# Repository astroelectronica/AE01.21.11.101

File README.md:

# AE01.21.11.101
MCP4531T-103E/MS
Basic configuration for Arduino UNO R3

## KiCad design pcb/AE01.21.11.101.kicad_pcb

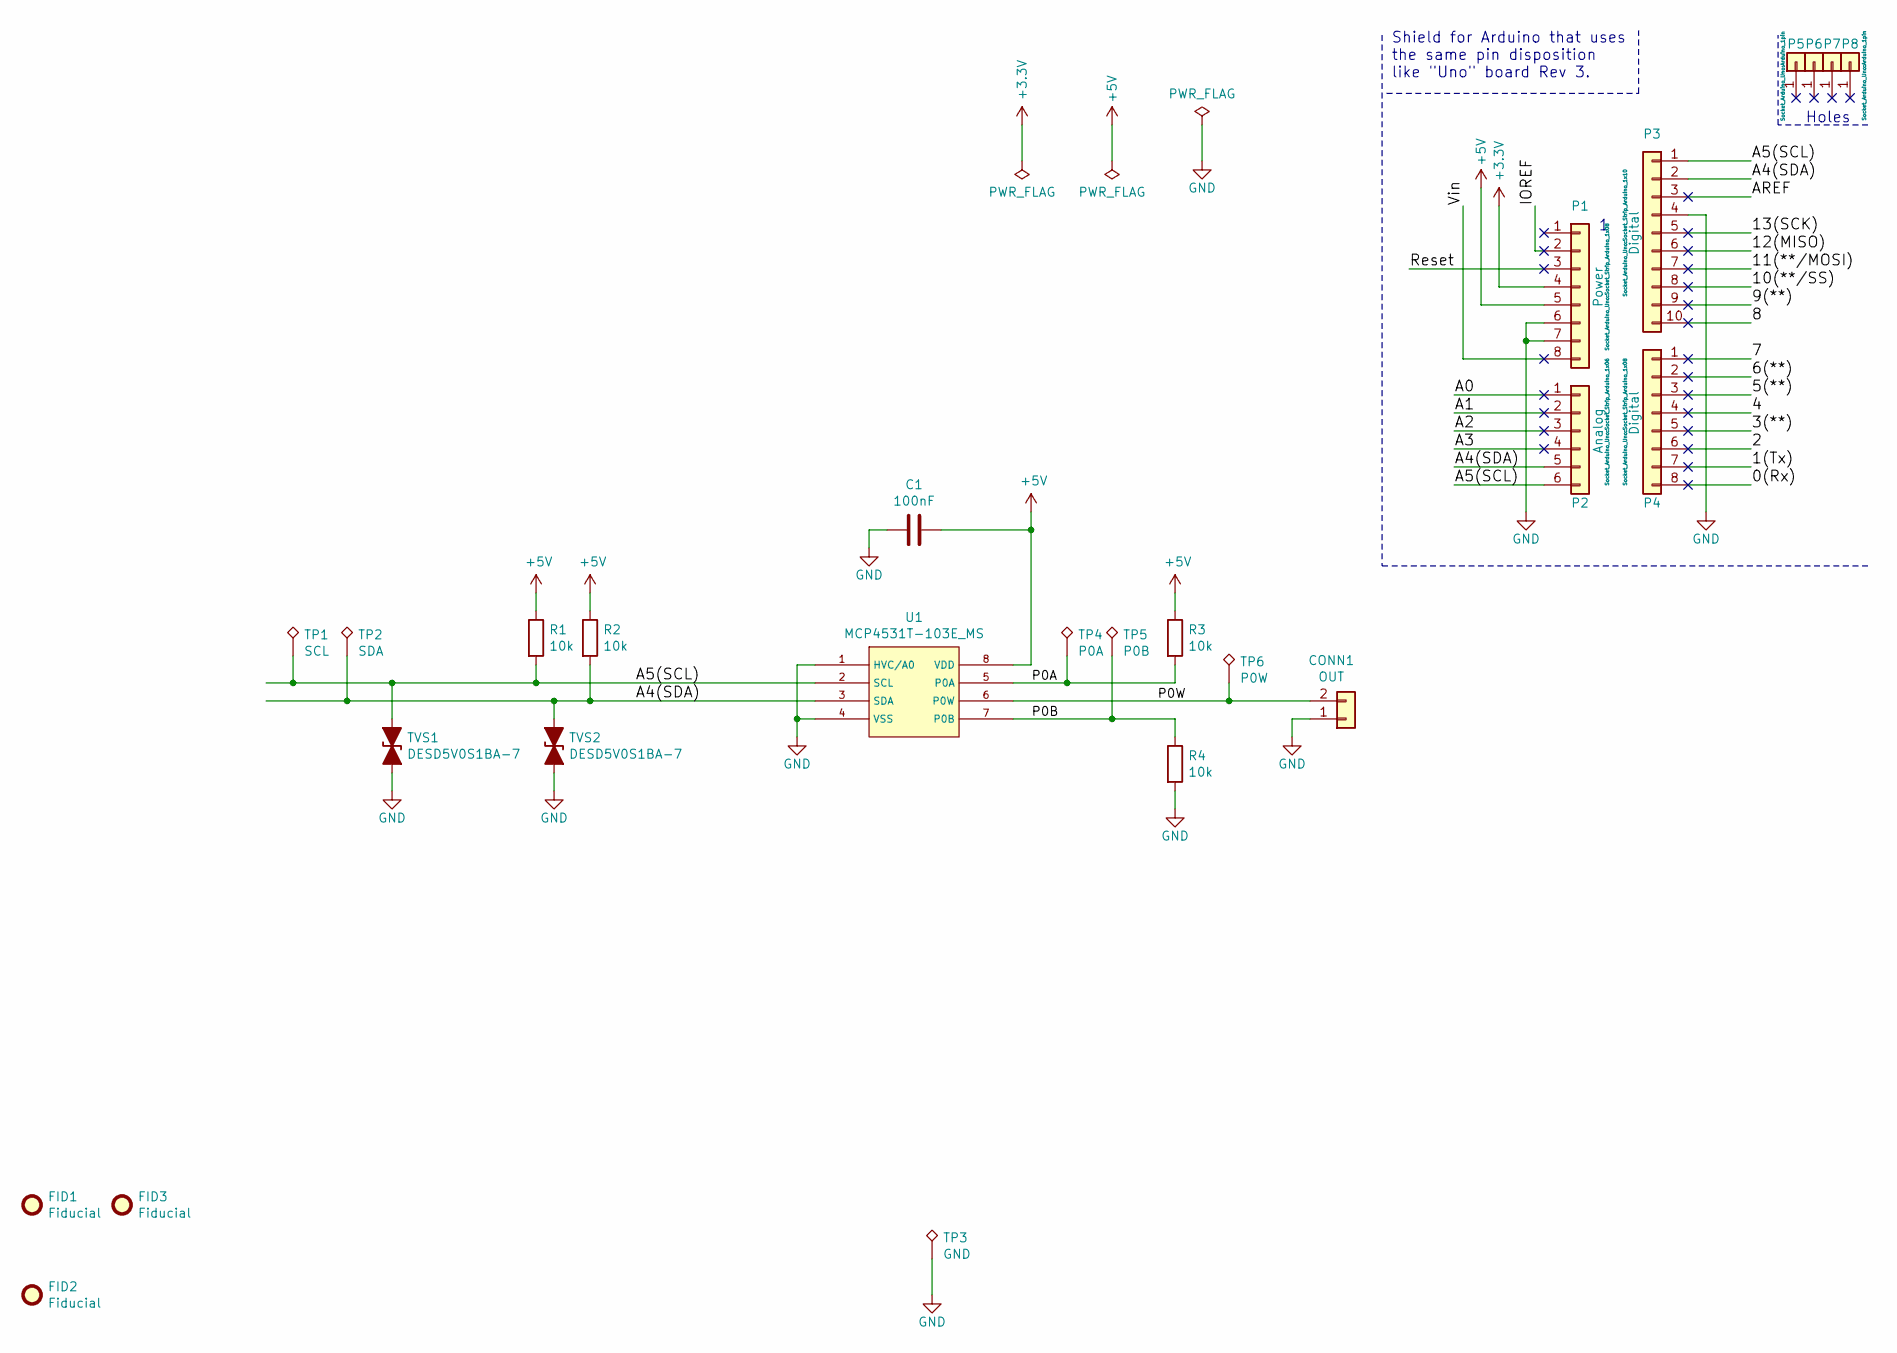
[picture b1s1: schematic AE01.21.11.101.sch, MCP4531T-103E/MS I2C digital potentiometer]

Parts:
C1: 100nF; C_0805_2012Metric; MPN C2012X7R2A104K125AA
CONN1: OUT; PinHeader_1x02_P2.54mm_Horizontal; MPN 0022289020
FID1, FID2, FID3: Fiducial; Fiducial_0.5mm_Mask1mm
P1: Power; Socket_Strip_Arduino_1x08
P2: Analog; Socket_Strip_Arduino_1x06
P3: Digital; Socket_Strip_Arduino_1x10
P4: Digital; Socket_Strip_Arduino_1x08
P5, P6, P7, P8: CONN_01X01; Arduino_1pin
R1, R2, R3, R4: 10k; R_0805_2012Metric; MPN RC0805FR-0710KL
TP1: SCL; TestPoint_Pad_D1.0mm
TP2: SDA; TestPoint_Pad_D1.0mm
TP3: GND; TestPoint_Keystone_5010-5014_Multipurpose; MPN 5011
TP4: P0A; TestPoint_Pad_D1.0mm
TP5: P0B; TestPoint_Pad_D1.0mm
TP6: P0W; TestPoint_Pad_D1.0mm
TVS1, TVS2: DESD5V0S1BA-7; D_SOD-323; MPN DESD5V0S1BA-7
U1: MCP4531T-103E_MS; MSOP-8_3x3mm_P0.65mm; MPN MCP4531T-103E/MS

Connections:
+3V3: P1.4
+5V: C1.1, P1.5, R1.1, R2.1, R3.1, U1.8 (VDD)
/0(Rx): P4.8
/1(Tx): P4.7
/2: P4.6
/3(**): P4.5
/4: P4.4
/5(**): P4.3
/6(**): P4.2
/7: P4.1
/8: P3.10
/9(**): P3.9
/10(**/SS): P3.8
/11(**/MOSI): P3.7
/12(MISO): P3.6
/13(SCK): P3.5
/A0: P2.1
/A1: P2.2
/A2: P2.3
/A3: P2.4
/A4(SDA): P2.5, P3.2, R2.2, TP2.1, TVS2.1 (A1), U1.3 (SDA)
/A5(SCL): P2.6, P3.1, R1.2, TP1.1, TVS1.1 (A1), U1.2 (SCL)
/AREF: P3.3
/IOREF: P1.2
/P0A: R3.2, TP4.1, U1.5 (P0A)
/P0B: R4.1, TP5.1, U1.7 (P0B)
/P0W: CONN1.2, TP6.1, U1.6 (P0W)
/Reset: P1.3
/Vin: P1.8
GND: C1.2, CONN1.1, P1.6, P1.7, P3.4, R4.2, TP3.1, TVS1.2 (A2), TVS2.2 (A2), U1.1 (HVC/A0), U1.4 (VSS)

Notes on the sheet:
Holes
Shield for Arduino that uses the same pin disposition like "Uno" board Rev 3.

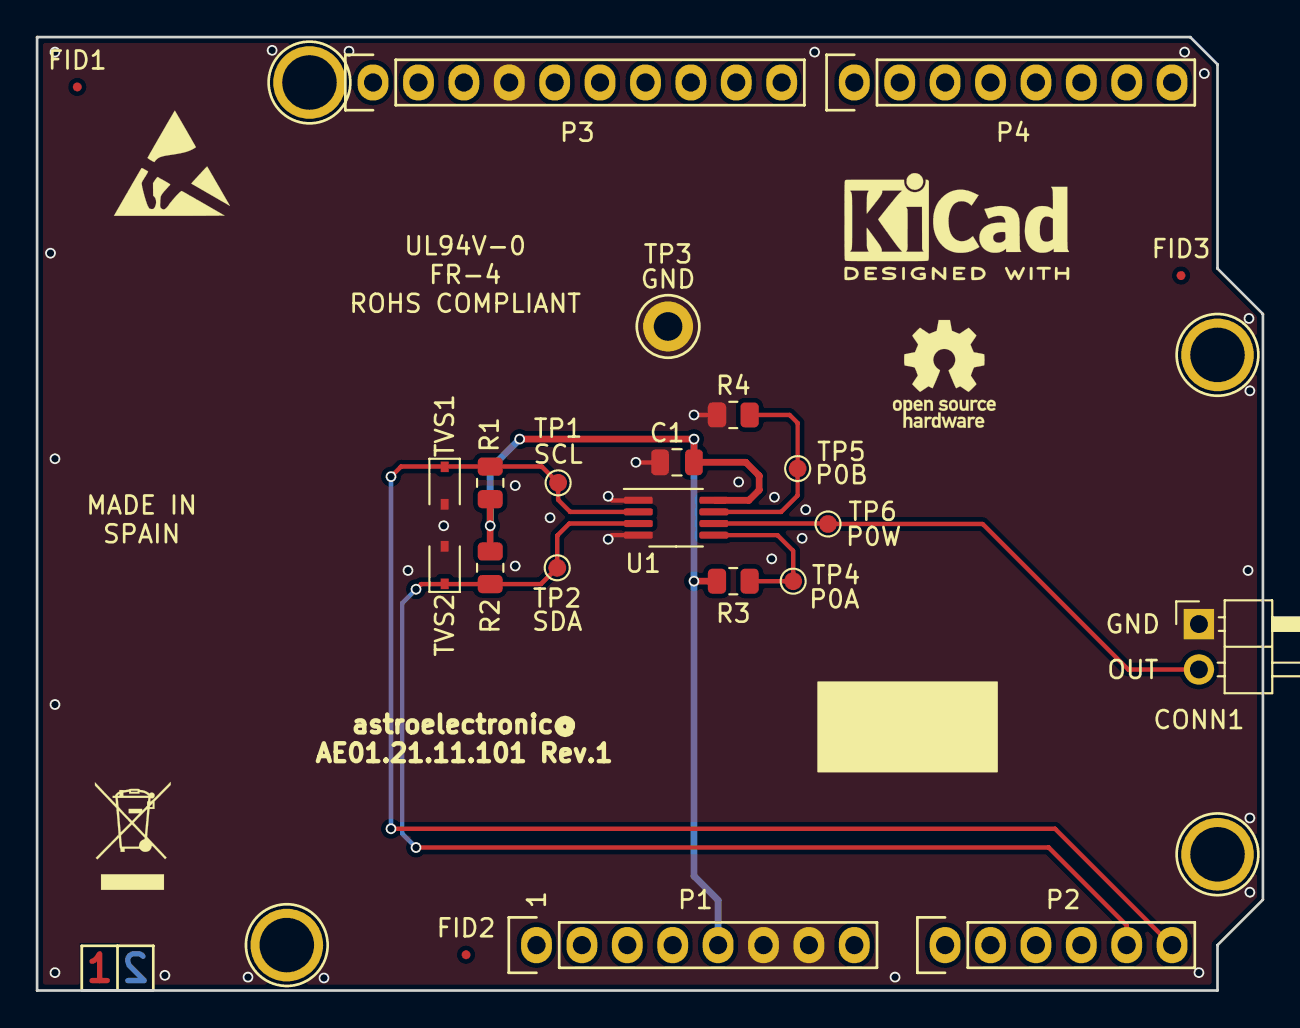
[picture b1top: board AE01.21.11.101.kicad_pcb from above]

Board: 2 copper layers, 68.6 x 53.3 mm, 26 parts (0 on the bottom side), 7 nets.

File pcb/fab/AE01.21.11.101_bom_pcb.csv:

Designator;Package;Quantity;Designation;Supplier and ref
C1;C_0805_2012Metric;1;100nF;
CONN1;PinHeader_1x02_P2.54mm_Horizontal;1;OUT;
FID1,FID2,FID3;Fiducial_0.5mm_Mask1mm;3;Fiducial;
P1;Socket_Strip_Arduino_1x08;1;Power;
P2;Socket_Strip_Arduino_1x06;1;Analog;
P3;Socket_Strip_Arduino_1x10;1;Digital;
P4;Socket_Strip_Arduino_1x08;1;Digital;
P5,P6,P7,P8;Arduino_1pin;4;CONN_01X01;
R1,R2,R3,R4;R_0805_2012Metric;4;10k;
REF**;KiCad-Logo2_5mm_SilkScreen;1;KiCad-Logo2_5mm_SilkScreen;
REF**;WEEE-Logo_4.2x6mm_SilkScreen;1;WEEE-Logo_4.2x6mm_SilkScreen;
REF**;OSHW-Logo_5.7x6mm_SilkScreen;1;OSHW-Logo_5.7x6mm_SilkScreen;
REF**;ESD-Logo_6.6x6mm_SilkScreen;1;ESD-Logo_6.6x6mm_SilkScreen;
TP1;TestPoint_Pad_D1.0mm;1;SCL;
TP2;TestPoint_Pad_D1.0mm;1;SDA;
TP3;TestPoint_Keystone_5010-5014_Multipurpose;1;GND;
TP4;TestPoint_Pad_D1.0mm;1;P0A;
TP5;TestPoint_Pad_D1.0mm;1;P0B;
TP6;TestPoint_Pad_D1.0mm;1;P0W;
TVS1,TVS2;D_SOD-323;2;DESD5V0S1BA-7;
U1;MSOP-8_3x3mm_P0.65mm;1;MCP4531T-103E_MS;
